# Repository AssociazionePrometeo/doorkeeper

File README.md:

# doorkeeper
Elettroserratura per IoT

Clone Project:

git clone --recursive https://github.com/AssociazionePrometeo/doorkeeper.git

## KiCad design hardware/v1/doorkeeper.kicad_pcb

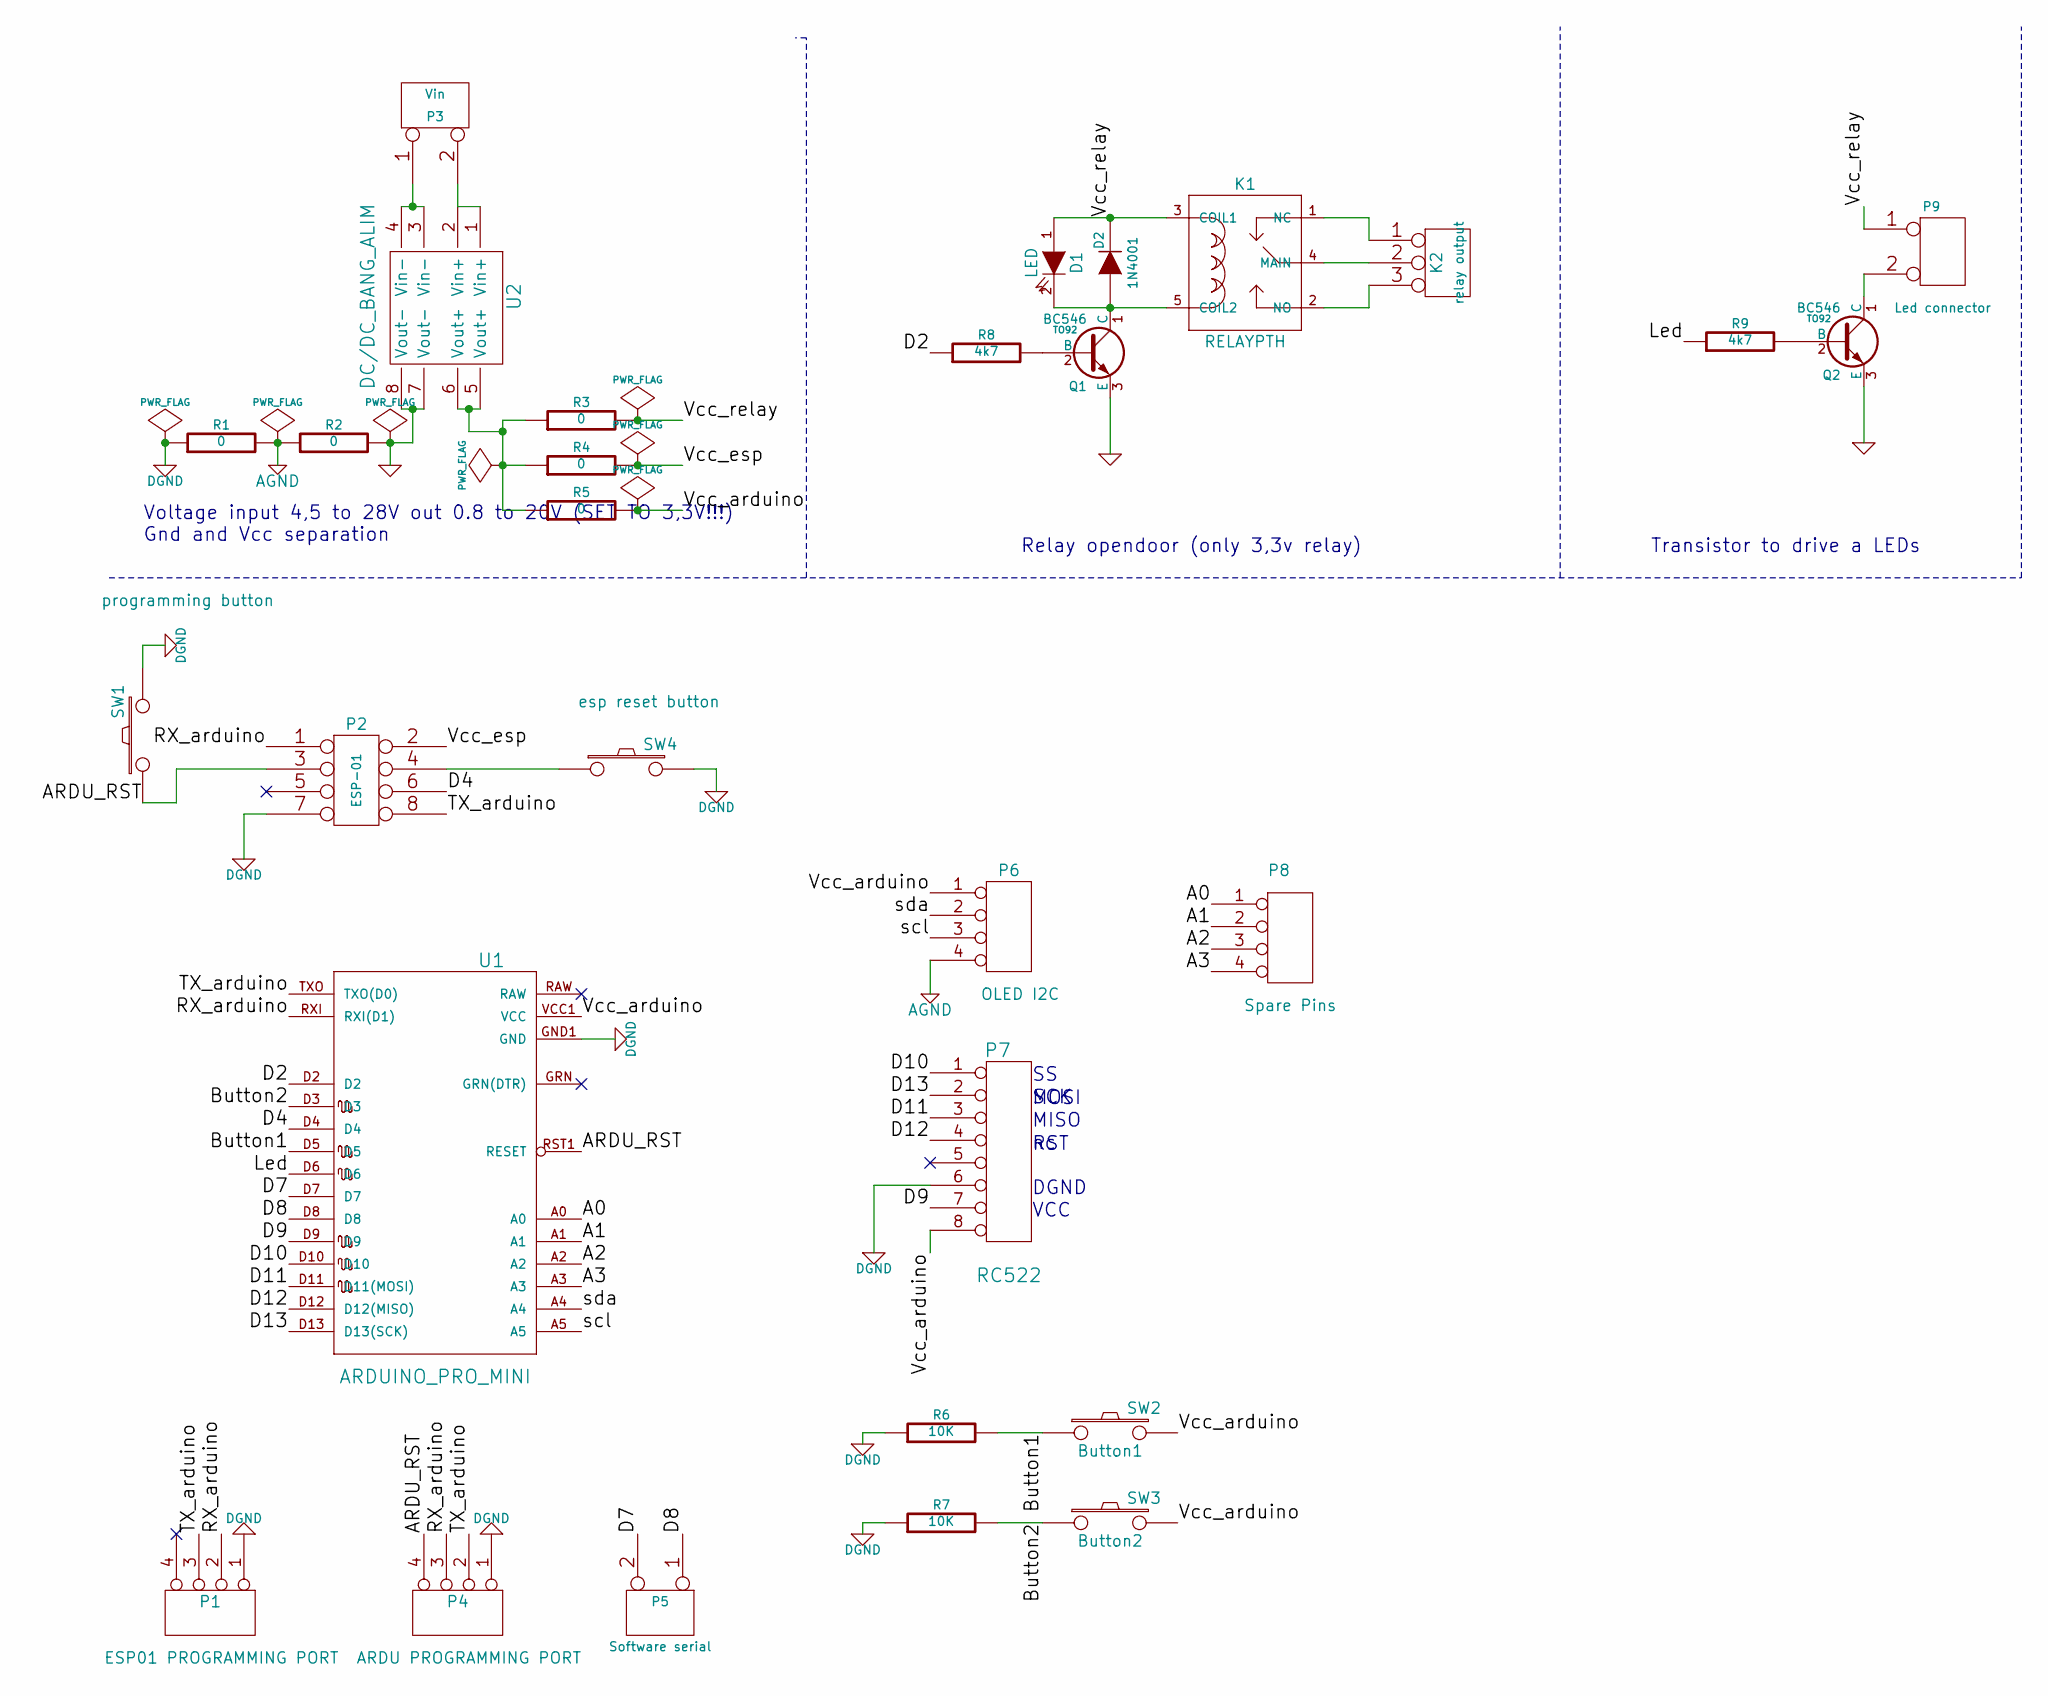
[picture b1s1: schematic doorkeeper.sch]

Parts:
D1: LED
D2: 1N4001
K1: RELAYPTH
K2: relay output
P1: ESP01 PROGRAMMING PORT
P2: ESP-01
P3: Vin
P4: ARDU PROGRAMMING PORT
P5: Software serial
P6: OLED I2C
P7: RC522
P8: Spare Pins
P9: Led connector
Q1, Q2: BC546; TO92
R1, R2, R3, R4, R5: 0
R6, R7: 10K
R8, R9: 4k7
SW1: programming button
SW2: Button1
SW3: Button2
SW4: esp reset button
U1: ARDUINO_PRO_MINI
U2: DC/DC_BANG_ALIM

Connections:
/A0: P8.1, U1.A0
/A1: P8.2, U1.A1
/A2: P8.3, U1.A2
/A3: P8.4, U1.A3
/ARDU_RST: P2.3 (CH_PD), P4.4, SW1.1, U1.RST1 (RESET)
/Button1: R6.2, SW2.1, U1.D5
/Button2: R7.2, SW3.1, U1.D3
/D2: R8.1, U1.D2
/D4: P2.6 (GPIO0), U1.D4
/D7: P5.2 (PM), U1.D7
/D8: P5.1, U1.D8
/D9: P7.7, U1.D9
/D10: P7.1, U1.D10
/D11: P7.3, U1.D11 (D11(MOSI))
/D12: P7.4, U1.D12 (D12(MISO))
/D13: P7.2, U1.D13 (D13(SCK))
/Led: R9.1, U1.D6
/RX_arduino: P1.2, P2.1 (UTXD), P4.3, U1.RXI (RXI(D1))
/TX_arduino: P1.3, P2.8 (URXD), P4.2, U1.TXO (TXO(D0))
/Vcc_arduino: P6.1, P7.8, R5.2, SW2.2, SW3.2, U1.VCC1 (VCC)
/Vcc_esp: P2.2 (DNG), R4.2
/Vcc_relay: D1.1 (A), D2.2 (K), K1.3 (COIL1), P9.1, R3.2
/scl: P6.3, U1.A5
/sda: P6.2, U1.A4
AGND: P6.4, R1.2, R2.1
DGND: P1.1, P2.7 (VCC), P4.1, P7.6, R1.1, R6.1, R7.1, SW1.2, SW4.2, U1.GND1 (GND)
GND: Q1.3 (E), Q2.3 (E), R2.2, U2.7 (Vout-), U2.8 (Vout-)
unnamed: Q2.2 (B), R9.2
unnamed: P9.2 (PM), Q2.1 (C)
unnamed: P2.4 (GPIO2), SW4.1
unnamed: Q1.2 (B), R8.2
unnamed: D1.2 (K), D2.1 (A), K1.5 (COIL2), Q1.1 (C)
unnamed: P3.2 (PM), U2.1 (Vin+), U2.2 (Vin+)
unnamed: P3.1, U2.3 (Vin-), U2.4 (Vin-)
unnamed: K1.2 (NO), K2.3
unnamed: K1.1 (NC), K2.1
unnamed: K1.4 (MAIN), K2.2 (PM)
unnamed: R3.1, R4.1, R5.1, U2.5 (Vout+), U2.6 (Vout+)

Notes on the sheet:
Voltage input 4,5 to 28V out 0.8 to 20V (SET TO 3,3V!!!) Gnd and Vcc separation
Relay opendoor (only 3,3v relay)
Transistor to drive a LEDs
SCK
MOSI
MISO
RST
VCC
DGND

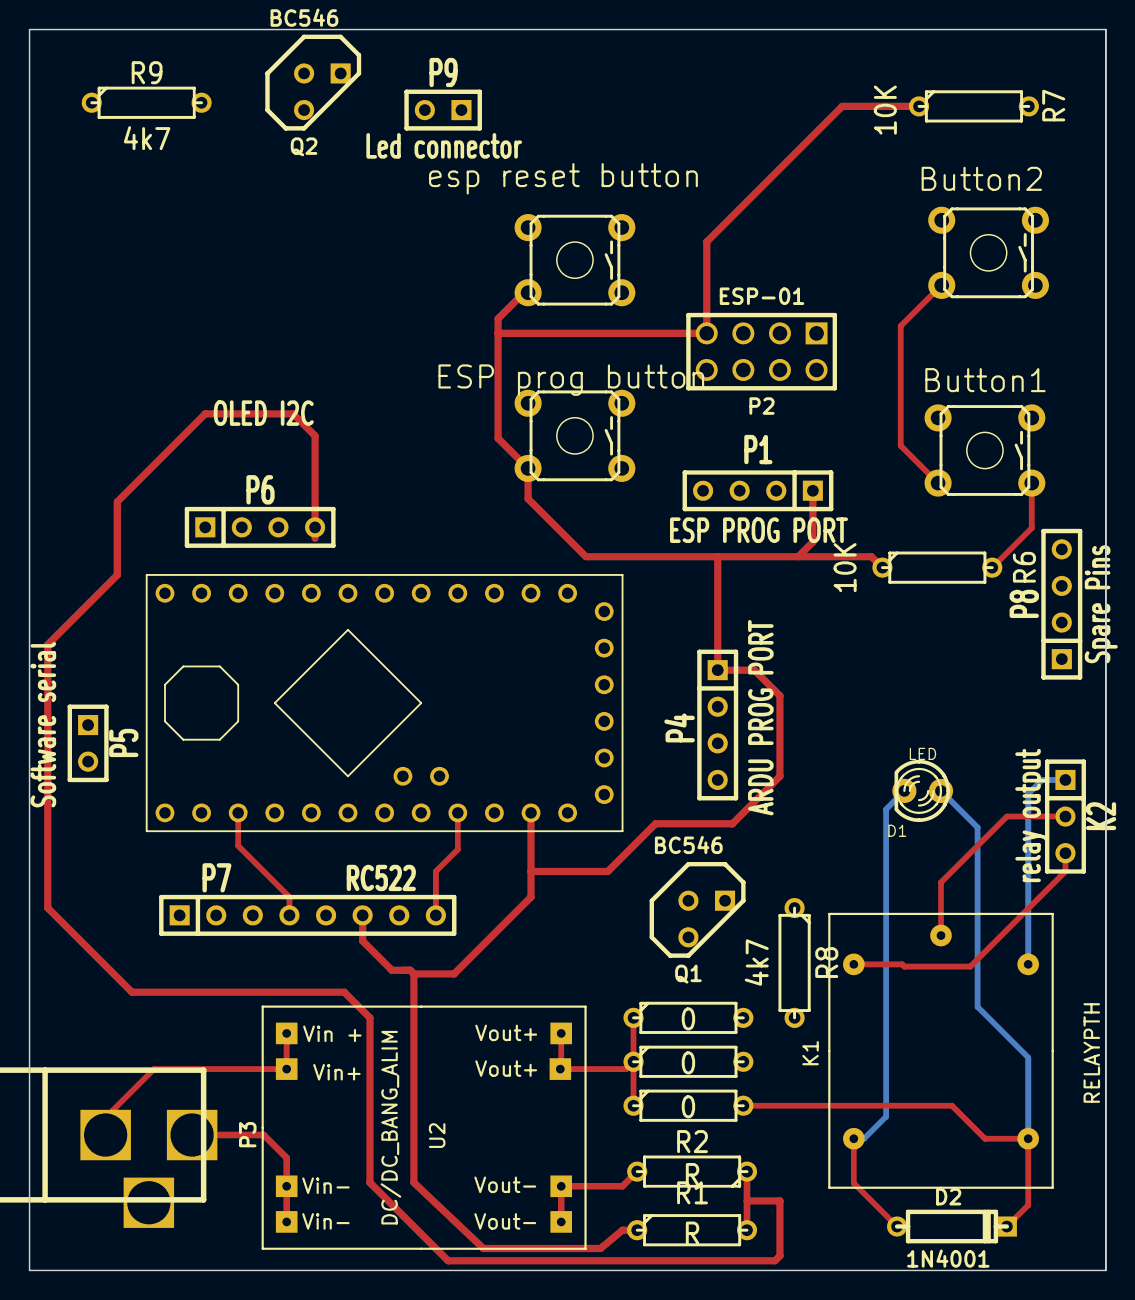
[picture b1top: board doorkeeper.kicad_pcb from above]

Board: 2 copper layers, 74.7 x 86.1 mm, 30 parts (0 on the bottom side), 38 nets.

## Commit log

2015-04-26 First import
2015-04-26 First import Arduino code
2015-04-26 Add doc
2015-04-26 Add hardaware
2015-05-03 change submodules url to https
2015-05-03 add readme
2015-05-05 first schematic only for testing not working
2015-05-06 corrected a schematic
2015-05-09 partial routing
2015-06-16 First dockerfiles for the mosquitto server and mariadb
2015-06-17 some changes to run with docker-compose
2015-06-19 fix typo
2015-06-21 Java mqtt client sample based on paho
2015-07-15 add .gitignore
2015-07-15 new prototype without arduino
2015-08-16 Add MQTT client and WIFI STA configuration
2015-08-16 remove arduino based old prototype
2015-08-16 add esp-mqtt-arduino library
2015-10-04 first implementation of the handle with mqtt calbacks. State: alpha
2015-10-21 first handle implementation
